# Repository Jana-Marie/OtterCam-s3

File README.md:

# OtterCam-s3

Open source 1080p60Hz USB & IP camera based on Sochip s3 and OS05A10/OS05A20 (general MIPI CSI IP camera interface).

In the current state the camera does boot and the sensor shows up under linux, however no video or image files have been captured yet, as the sensor driver is currently being written by us. All hardware files are tested in the current revision and are, except for some minor changes, final. Still no waranty as this is an open source project. CAD files have been designed with OpenSCAD and should be final too.

<table>
  <tbody>
    <tr>
      <td>
        
      </td>
      <td>
        
      </td>
    </tr>
    <tr>
      <td colspan="2">
        
      </td>
    </tr>
    <tr>
      <td>
        
      </td>
      <td>
        
      </td>
    </tr>
  </tbody>
</table>

### Todo
 - [ ] Test mipi driver
 - [ ] Build userspace code

### Issues
 - [x] MIPI Lanes Sensor are switched
 - [x] No I2C Pullups

### License

Copyright Jana Marie Hemsing 2023.

This source describes Open Hardware and is licensed under the CERN-OHL-S v2.

You may redistribute and modify this source and make products using it under
the terms of the CERN-OHL-S v2 (https://ohwr.org/cern_ohl_s_v2.txt).

This source is distributed WITHOUT ANY EXPRESS OR IMPLIED WARRANTY,
INCLUDING OF MERCHANTABILITY, SATISFACTORY QUALITY AND FITNESS FOR A
PARTICULAR PURPOSE. Please see the CERN-OHL-S v2 for applicable conditions.

Source location: https://github.com/Jana-Marie/OtterCam-s3

As per CERN-OHL-S v2 section 4, should You produce hardware based on this
source, You must where practicable maintain the Source Location visible
on the external case of the Gizmo or other products you make using this
source.

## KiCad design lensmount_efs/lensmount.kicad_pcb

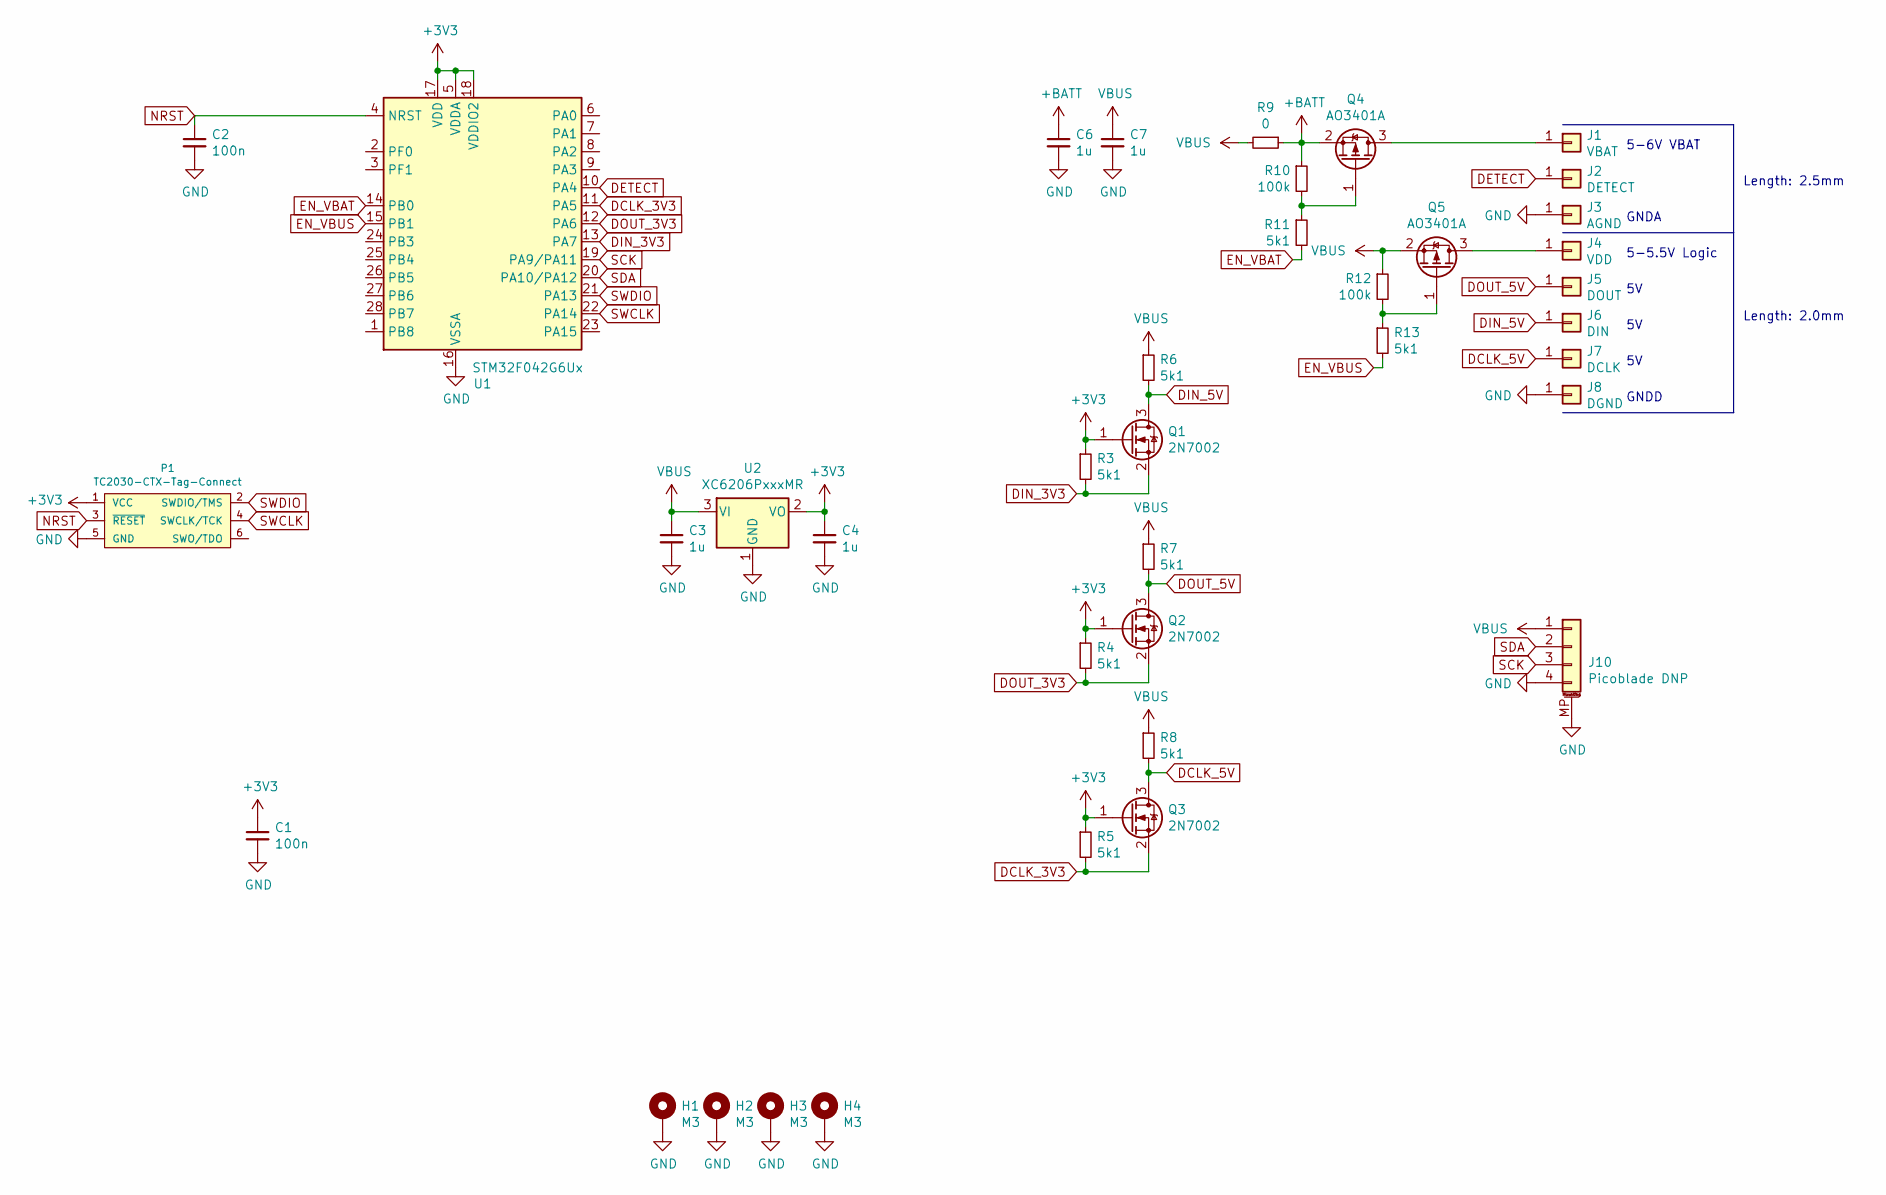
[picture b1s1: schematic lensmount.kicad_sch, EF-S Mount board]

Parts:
C1, C2: 100n; C_0402
C3, C4, C6, C7: 1u; C_0603
H1, H2, H3, H4: M3; MountingHole_3mm_Pad_Via
J1: VBAT; PH-MVF-5365; Mouser 581-709150001025006
J2: DETECT; PH-MVF-5365; Mouser 581-709150001025006
J3: AGND; PH-MVF-5365; Mouser 581-709150001025006
J4: VDD; PH-MVF-5365; Mouser 581-709150001020006
J5: DOUT; PH-MVF-5365; Mouser 581-709150001020006
J6: DIN; PH-MVF-5365; Mouser 581-709150001020006
J7: DCLK; PH-MVF-5365; Mouser 581-709150001020006
J8: DGND; PH-MVF-5365; Mouser 581-709150001020006
J10: Picoblade DNP; Molex_PicoBlade_53398-0471_1x04-1MP_P1.25mm_Vertical
P1: TC2030-CTX-Tag-Connect; TC2030
Q1, Q2, Q3: 2N7002; SOT-23
Q4, Q5: AO3401A; SOT-23
R3, R4, R5, R6, R7, R8, R11, R13: 5k1; R_0402
R9: 0; R_0402
R10, R12: 100k; R_0402
U1: STM32F042G6Ux; QFN-28_4x4mm_P0.5mm
U2: XC6206PxxxMR; SOT-23

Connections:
+3V3: C1.1, C4.1, P1.1 (VCC), Q1.1 (G), Q2.1 (G), Q3.1 (G), R3.1, R4.1, R5.1, U1.5 (VDDA), U1.17 (VDD), U1.18 (VDDIO2), U2.2 (VO)
+BATT: C6.1, Q4.2 (S), R9.1, R10.1
DCLK_3V3: Q3.2 (S), R5.2, U1.11 (PA5)
DCLK_5V: J7.1, Q3.3 (D), R8.2
DETECT: J2.1, U1.10 (PA4)
DIN_3V3: Q1.2 (S), R3.2, U1.13 (PA7)
DIN_5V: J6.1, Q1.3 (D), R6.2
DOUT_3V3: Q2.2 (S), R4.2, U1.12 (PA6)
DOUT_5V: J5.1, Q2.3 (D), R7.2
EN_VBAT: R11.2, U1.14 (PB0)
EN_VBUS: R13.2, U1.15 (PB1)
GND: C1.2, C2.2, C3.2, C4.2, C6.2, C7.2, H1.1, H2.1, H3.1, H4.1, J3.1, J8.1, J10.4, J10.MP (MountPin), P1.5 (GND), U1.16 (VSSA), U2.1 (GND)
NRST: C2.1, P1.3 (~RESET), U1.4 (NRST)
unnamed: J1.1, Q4.3 (D)
unnamed: J4.1, Q5.3 (D)
unnamed: Q4.1 (G), R10.2, R11.1
unnamed: Q5.1 (G), R12.2, R13.1
SCK: J10.3, U1.19 (PA9/PA11)
SDA: J10.2, U1.20 (PA10/PA12)
SWCLK: P1.4 (SWCLK/TCK), U1.22 (PA14)
SWDIO: P1.2 (SWDIO/TMS), U1.21 (PA13)
VBUS: C3.1, C7.1, J10.1, Q5.2 (S), R6.1, R7.1, R8.1, R9.2, R12.1, U2.3 (VI)

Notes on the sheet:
GNDD
5-6V VBAT
Length: 2.5mm
5-5.5V Logic
GNDA
Length: 2.0mm

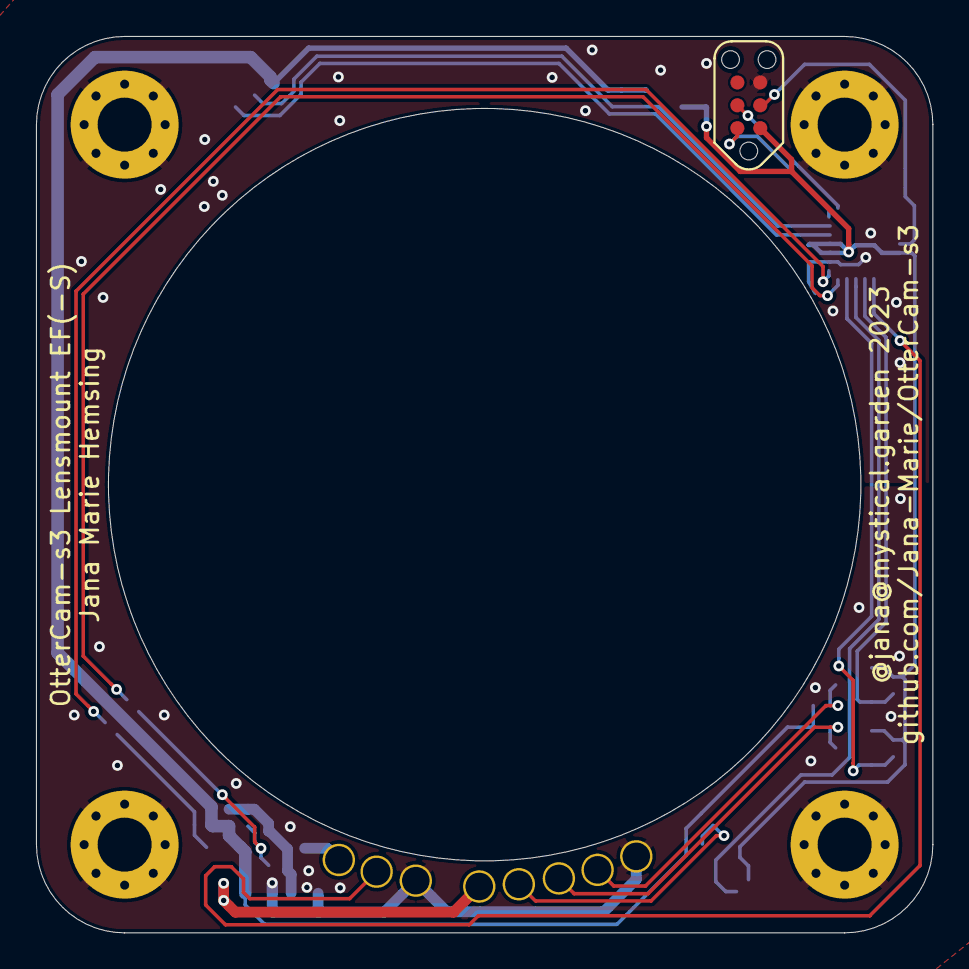
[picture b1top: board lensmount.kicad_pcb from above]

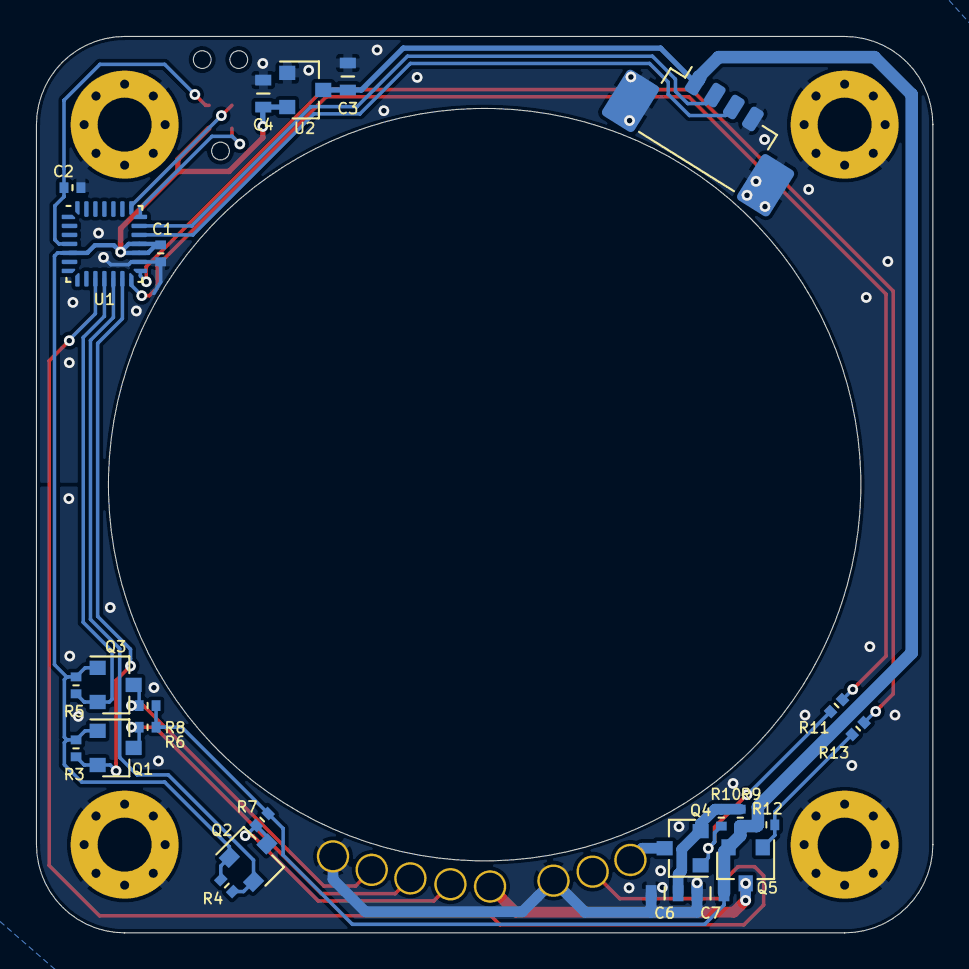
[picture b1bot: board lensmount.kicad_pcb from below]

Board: 2 copper layers, 49.8 x 49.8 mm, 38 parts (25 on the bottom side), 22 nets.

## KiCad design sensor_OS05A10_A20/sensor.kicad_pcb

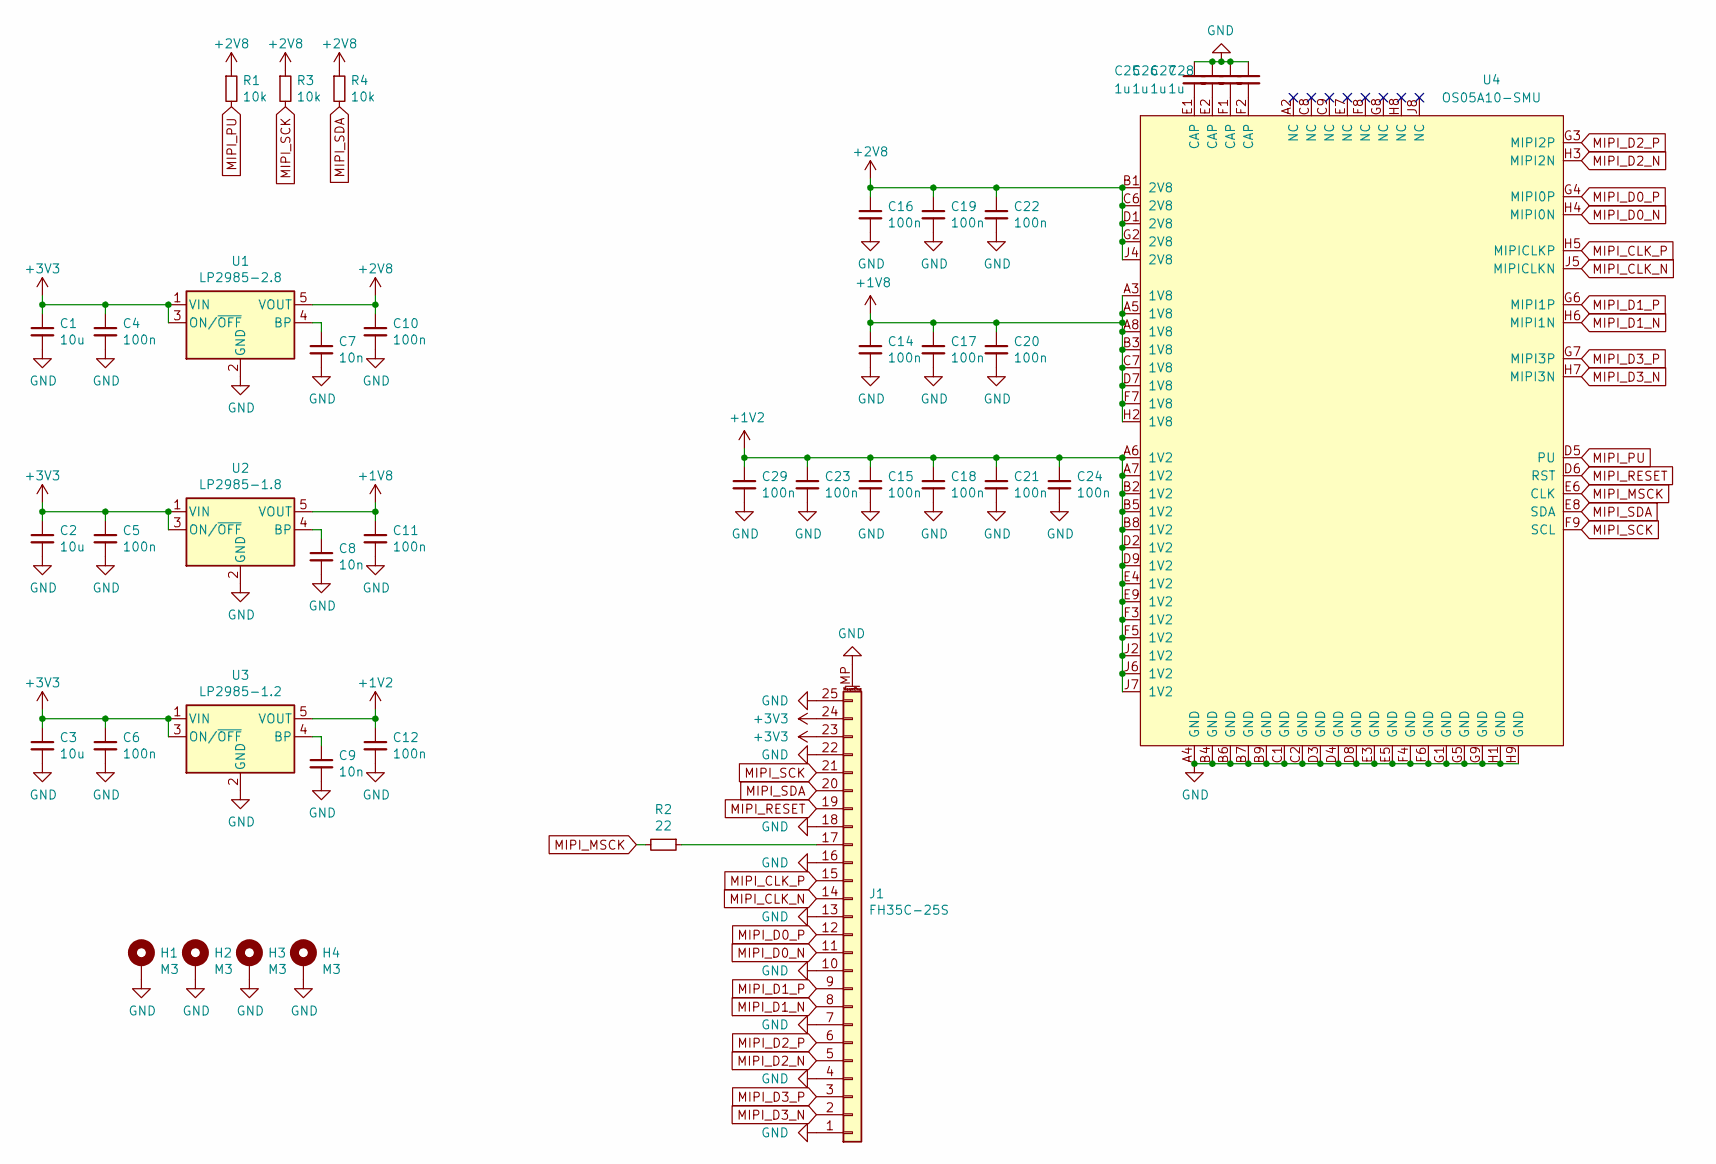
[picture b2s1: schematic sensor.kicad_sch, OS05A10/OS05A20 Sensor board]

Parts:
C1, C2, C3: 10u; C_0603
C4, C5, C6, C10, C11, C12, C14, C15, C16, C17, C18, C19, C20, C21, C22, C23, C24, C29: 100n; C_0402
C7, C8, C9: 10n; C_0402
C25, C26, C27, C28: 1u; C_0402
H1, H2, H3, H4: M3; MountingHole_3mm_Pad_Via
J1: FH35C-25S
R1, R3, R4: 10k; R_0402
R2: 22; R_0402
U1: LP2985-2.8; SOT-23-5
U2: LP2985-1.8; SOT-23-5
U3: LP2985-1.2; SOT-23-5
U4: OS05A10-SMU; OS05A10

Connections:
+1V2: C12.1, C15.1, C18.1, C21.1, C23.1, C24.1, C29.1, U3.5 (VOUT), U4.A6 (1V2), U4.A7 (1V2), U4.B2 (1V2), U4.B5 (1V2), U4.B8 (1V2), U4.D2 (1V2), U4.D9 (1V2), U4.E4 (1V2), U4.E9 (1V2), U4.F3 (1V2), U4.F5 (1V2), U4.J2 (1V2), U4.J6 (1V2), U4.J7 (1V2)
+1V8: C11.1, C14.1, C17.1, C20.1, U2.5 (VOUT), U4.A3 (1V8), U4.A5 (1V8), U4.A8 (1V8), U4.B3 (1V8), U4.C7 (1V8), U4.D7 (1V8), U4.F7 (1V8), U4.H2 (1V8)
+2V8: C10.1, C16.1, C19.1, C22.1, R1.1, R3.1, R4.1, U1.5 (VOUT), U4.B1 (2V8), U4.C6 (2V8), U4.D1 (2V8), U4.G2 (2V8), U4.J4 (2V8)
+3V3: C1.1, C2.1, C3.1, C4.1, C5.1, C6.1, J1.23, J1.24, U1.1 (VIN), U1.3 (ON/~OFF), U2.1 (VIN), U2.3 (ON/~OFF), U3.1 (VIN), U3.3 (ON/~OFF)
GND: C1.2, C2.2, C3.2, C4.2, C5.2, C6.2, C7.2, C8.2, C9.2, C10.2, C11.2, C12.2, C14.2, C15.2, C16.2, C17.2, C18.2, C19.2, C20.2, C21.2, C22.2, C23.2, C24.2, C25.1, C26.1, C27.1, C28.1, C29.2, H1.1, H2.1, H3.1, H4.1, J1.1, J1.4, J1.7, J1.10, J1.13, J1.16, J1.18, J1.22, J1.25, J1.MP (MountPin), U1.2 (GND), U2.2 (GND), U3.2 (GND), U4.A4 (GND), U4.B4 (GND), U4.B6 (GND), U4.B7 (GND), U4.B9 (GND), U4.C1 (GND), U4.C2 (GND), U4.D3 (GND), U4.D4 (GND), U4.D8 (GND), U4.E3 (GND), U4.E5 (GND), U4.F4 (GND), U4.F6 (GND), U4.G1 (GND), U4.G5 (GND), U4.G9 (GND), U4.H1 (GND), U4.H9 (GND)
MIPI_CLK_N: J1.14, U4.J5 (MIPICLKN)
MIPI_CLK_P: J1.15, U4.H5 (MIPICLKP)
MIPI_D0_N: J1.11, U4.H4 (MIPI0N)
MIPI_D0_P: J1.12, U4.G4 (MIPI0P)
MIPI_D1_N: J1.8, U4.H6 (MIPI1N)
MIPI_D1_P: J1.9, U4.G6 (MIPI1P)
MIPI_D2_N: J1.5, U4.H3 (MIPI2N)
MIPI_D2_P: J1.6, U4.G3 (MIPI2P)
MIPI_D3_N: J1.2, U4.H7 (MIPI3N)
MIPI_D3_P: J1.3, U4.G7 (MIPI3P)
MIPI_MSCK: R2.2, U4.E6 (CLK)
MIPI_PU: R1.2, U4.D5 (PU)
MIPI_RESET: J1.19, U4.D6 (RST)
MIPI_SCK: J1.21, R3.2, U4.F9 (SCL)
MIPI_SDA: J1.20, R4.2, U4.E8 (SDA)
unnamed: C7.1, U1.4 (BP)
unnamed: C8.1, U2.4 (BP)
unnamed: C9.1, U3.4 (BP)
unnamed: C25.2, U4.E1 (CAP)
unnamed: C26.2, U4.E2 (CAP)
unnamed: C27.2, U4.F1 (CAP)
unnamed: C28.2, U4.F2 (CAP)
unnamed: J1.17, R2.1

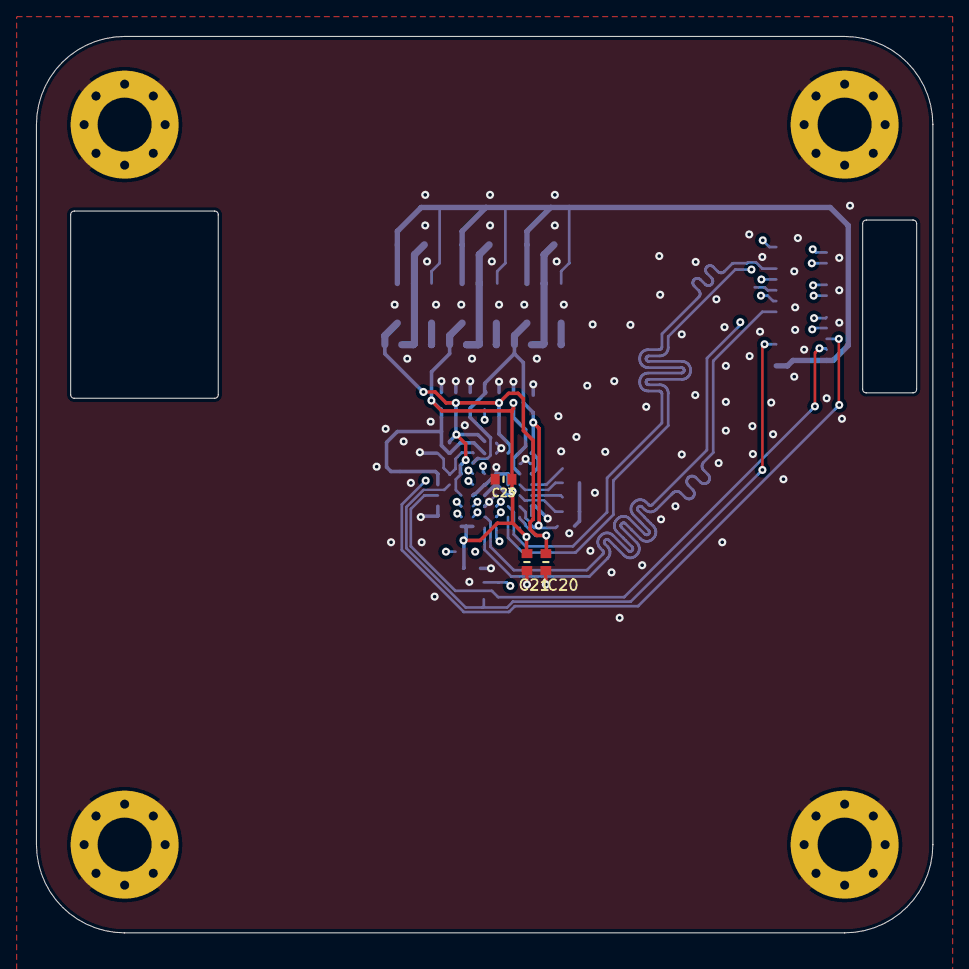
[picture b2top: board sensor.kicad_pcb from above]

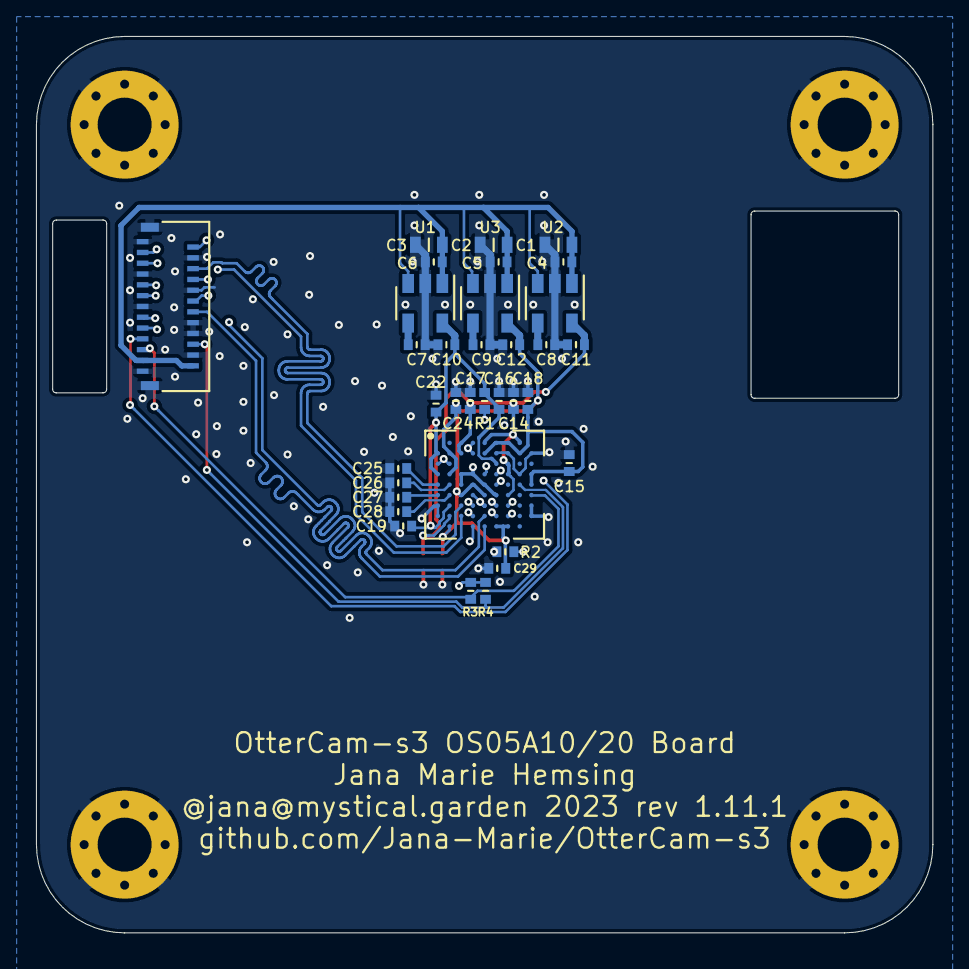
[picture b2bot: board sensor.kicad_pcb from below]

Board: 4 copper layers, 49.8 x 49.8 mm, 41 parts (38 on the bottom side), 28 nets.

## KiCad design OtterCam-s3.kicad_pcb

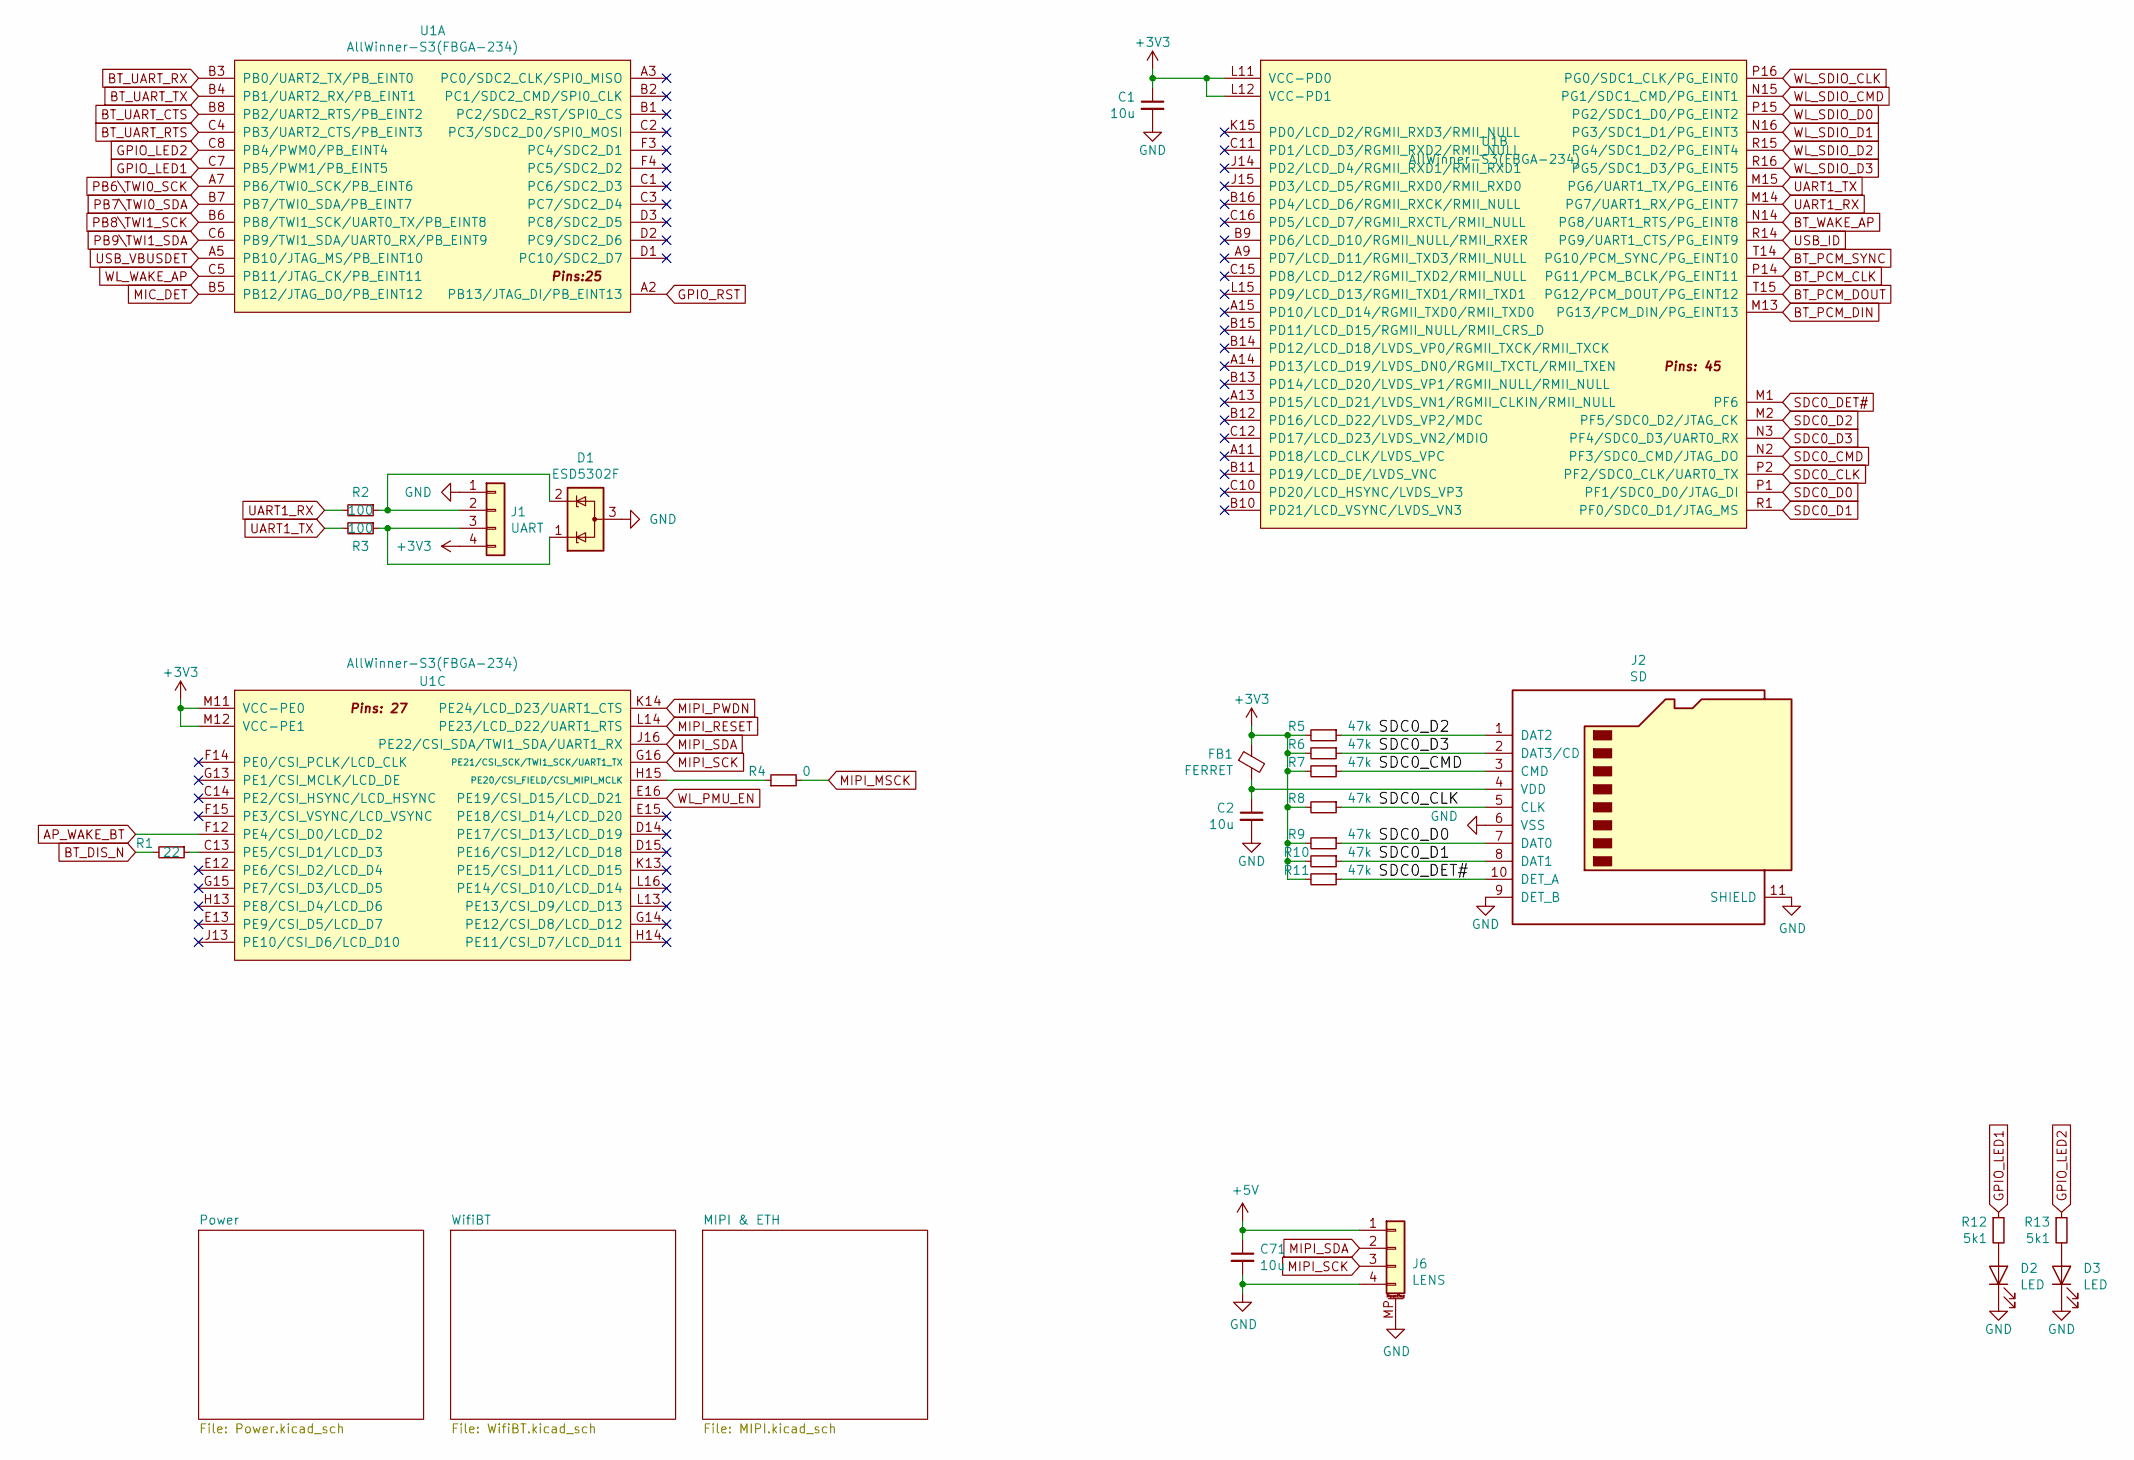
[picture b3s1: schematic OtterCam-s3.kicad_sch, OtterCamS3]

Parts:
C1, C2, C71: 10u; C_0603
D1: ESD5302F; SOT-23; LCSC C239643
D2, D3: LED; LED_0603_1608Metric
FB1: FERRET; R_0805
J1: UART; PinHeader_1x04_P2.00mm_Vertical_nosilk_center
J2: SD; microSD_HC_Hirose_DM3D-SF
J6: LENS; Molex_PicoBlade_53398-0471_1x04-1MP_P1.25mm_Vertical
R1: 22; R_0402
R2, R3: 100; R_0402
R4: 0; R_0402
R5, R6, R7, R8, R9, R10, R11: 47k; R_0402
R12, R13: 5k1; R_0402
U1: AllWinner-S3(FBGA-234); FBGA-234(Pitch-0.65mm_Pad-0.3mm_11x11x1.08mm)

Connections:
+3V3: C1.1, FB1.1, J1.4, R5.2, R6.2, R7.2, R8.2, R9.2, R10.2, R11.2, U1.L11 (VCC-PD0), U1.L12 (VCC-PD1), U1.M11 (VCC-PE0), U1.M12 (VCC-PE1); also elsewhere on the board
+5V: C71.1, J6.1; also elsewhere on the board
AP_WAKE_BT: U1.F12 (PE4/CSI_D0/LCD_D2); also elsewhere on the board
BT_DIS_N: R1.2; also elsewhere on the board
BT_PCM_CLK: U1.P14 (PG11/PCM_BCLK/PG_EINT11)
BT_PCM_DIN: U1.M13 (PG13/PCM_DIN/PG_EINT13)
BT_PCM_DOUT: U1.T15 (PG12/PCM_DOUT/PG_EINT12)
BT_PCM_SYNC: U1.T14 (PG10/PCM_SYNC/PG_EINT10)
BT_UART_CTS: U1.B8 (PB2/UART2_RTS/PB_EINT2); also elsewhere on the board
BT_UART_RTS: U1.C4 (PB3/UART2_CTS/PB_EINT3); also elsewhere on the board
BT_UART_RX: U1.B3 (PB0/UART2_TX/PB_EINT0); also elsewhere on the board
BT_UART_TX: U1.B4 (PB1/UART2_RX/PB_EINT1); also elsewhere on the board
BT_WAKE_AP: U1.N14 (PG8/UART1_RTS/PG_EINT8); also elsewhere on the board
GND: C1.2, C2.2, C71.2, D1.3 (A), D2.1 (K), D3.1 (K), J1.1, J2.6 (VSS), J2.9 (DET_B), J2.11 (SHIELD), J6.4, J6.MP (MountPin); also elsewhere on the board
GPIO_LED1: R12.1, U1.C7 (PB5/PWM1/PB_EINT5)
GPIO_LED2: R13.1, U1.C8 (PB4/PWM0/PB_EINT4)
GPIO_RST: U1.A2 (PB13/JTAG_DI/PB_EINT13); also elsewhere on the board
MIC_DET: U1.B5 (PB12/JTAG_DO/PB_EINT12)
MIPI_MSCK: R4.2; also elsewhere on the board
MIPI_PWDN: U1.K14 (PE24/LCD_D23/UART1_CTS)
MIPI_RESET: U1.L14 (PE23/LCD_D22/UART1_RTS); also elsewhere on the board
MIPI_SCK: J6.3, U1.G16 (PE21/CSI_SCK/TWI1_SCK/UART1_TX); also elsewhere on the board
MIPI_SDA: J6.2, U1.J16 (PE22/CSI_SDA/TWI1_SDA/UART1_RX); also elsewhere on the board
unnamed: C2.1, FB1.2, J2.4 (VDD)
unnamed: D1.1 (K), J1.3, R3.1
unnamed: D1.2 (K), J1.2, R2.1
unnamed: D2.2 (A), R12.2
unnamed: D3.2 (A), R13.2
unnamed: R1.1, U1.C13 (PE5/CSI_D1/LCD_D3)
unnamed: R4.1, U1.H15 (PE20/CSI_FIELD/CSI_MIPI_MCLK)
PB6\TWI0_SCK: U1.A7 (PB6/TWI0_SCK/PB_EINT6)
PB7\TWI0_SDA: U1.B7 (PB7/TWI0_SDA/PB_EINT7)
PB8\TWI1_SCK: U1.B6 (PB8/TWI1_SCK/UART0_TX/PB_EINT8)
PB9\TWI1_SDA: U1.C6 (PB9/TWI1_SDA/UART0_RX/PB_EINT9)
SDC0_CLK: J2.5 (CLK), R8.1, U1.P2 (PF2/SDC0_CLK/UART0_TX)
SDC0_CMD: J2.3 (CMD), R7.1, U1.N2 (PF3/SDC0_CMD/JTAG_DO)
SDC0_D0: J2.7 (DAT0), R9.1, U1.P1 (PF1/SDC0_D0/JTAG_DI)
SDC0_D1: J2.8 (DAT1), R10.1, U1.R1 (PF0/SDC0_D1/JTAG_MS)
SDC0_D2: J2.1 (DAT2), R5.1, U1.M2 (PF5/SDC0_D2/JTAG_CK)
SDC0_D3: J2.2 (DAT3/CD), R6.1, U1.N3 (PF4/SDC0_D3/UART0_RX)
SDC0_DET#: J2.10 (DET_A), R11.1, U1.M1 (PF6)
UART1_RX: R2.2, U1.M14 (PG7/UART1_RX/PG_EINT7)
UART1_TX: R3.2, U1.M15 (PG6/UART1_TX/PG_EINT6)
USB_ID: U1.R14 (PG9/UART1_CTS/PG_EINT9); also elsewhere on the board
USB_VBUSDET: U1.A5 (PB10/JTAG_MS/PB_EINT10)
WL_PMU_EN: U1.E16 (PE19/CSI_D15/LCD_D21); also elsewhere on the board
WL_SDIO_CLK: U1.P16 (PG0/SDC1_CLK/PG_EINT0); also elsewhere on the board
WL_SDIO_CMD: U1.N15 (PG1/SDC1_CMD/PG_EINT1); also elsewhere on the board
WL_SDIO_D0: U1.P15 (PG2/SDC1_D0/PG_EINT2); also elsewhere on the board
WL_SDIO_D1: U1.N16 (PG3/SDC1_D1/PG_EINT3); also elsewhere on the board
WL_SDIO_D2: U1.R15 (PG4/SDC1_D2/PG_EINT4); also elsewhere on the board
WL_SDIO_D3: U1.R16 (PG5/SDC1_D3/PG_EINT5); also elsewhere on the board
WL_WAKE_AP: U1.C5 (PB11/JTAG_CK/PB_EINT11); also elsewhere on the board

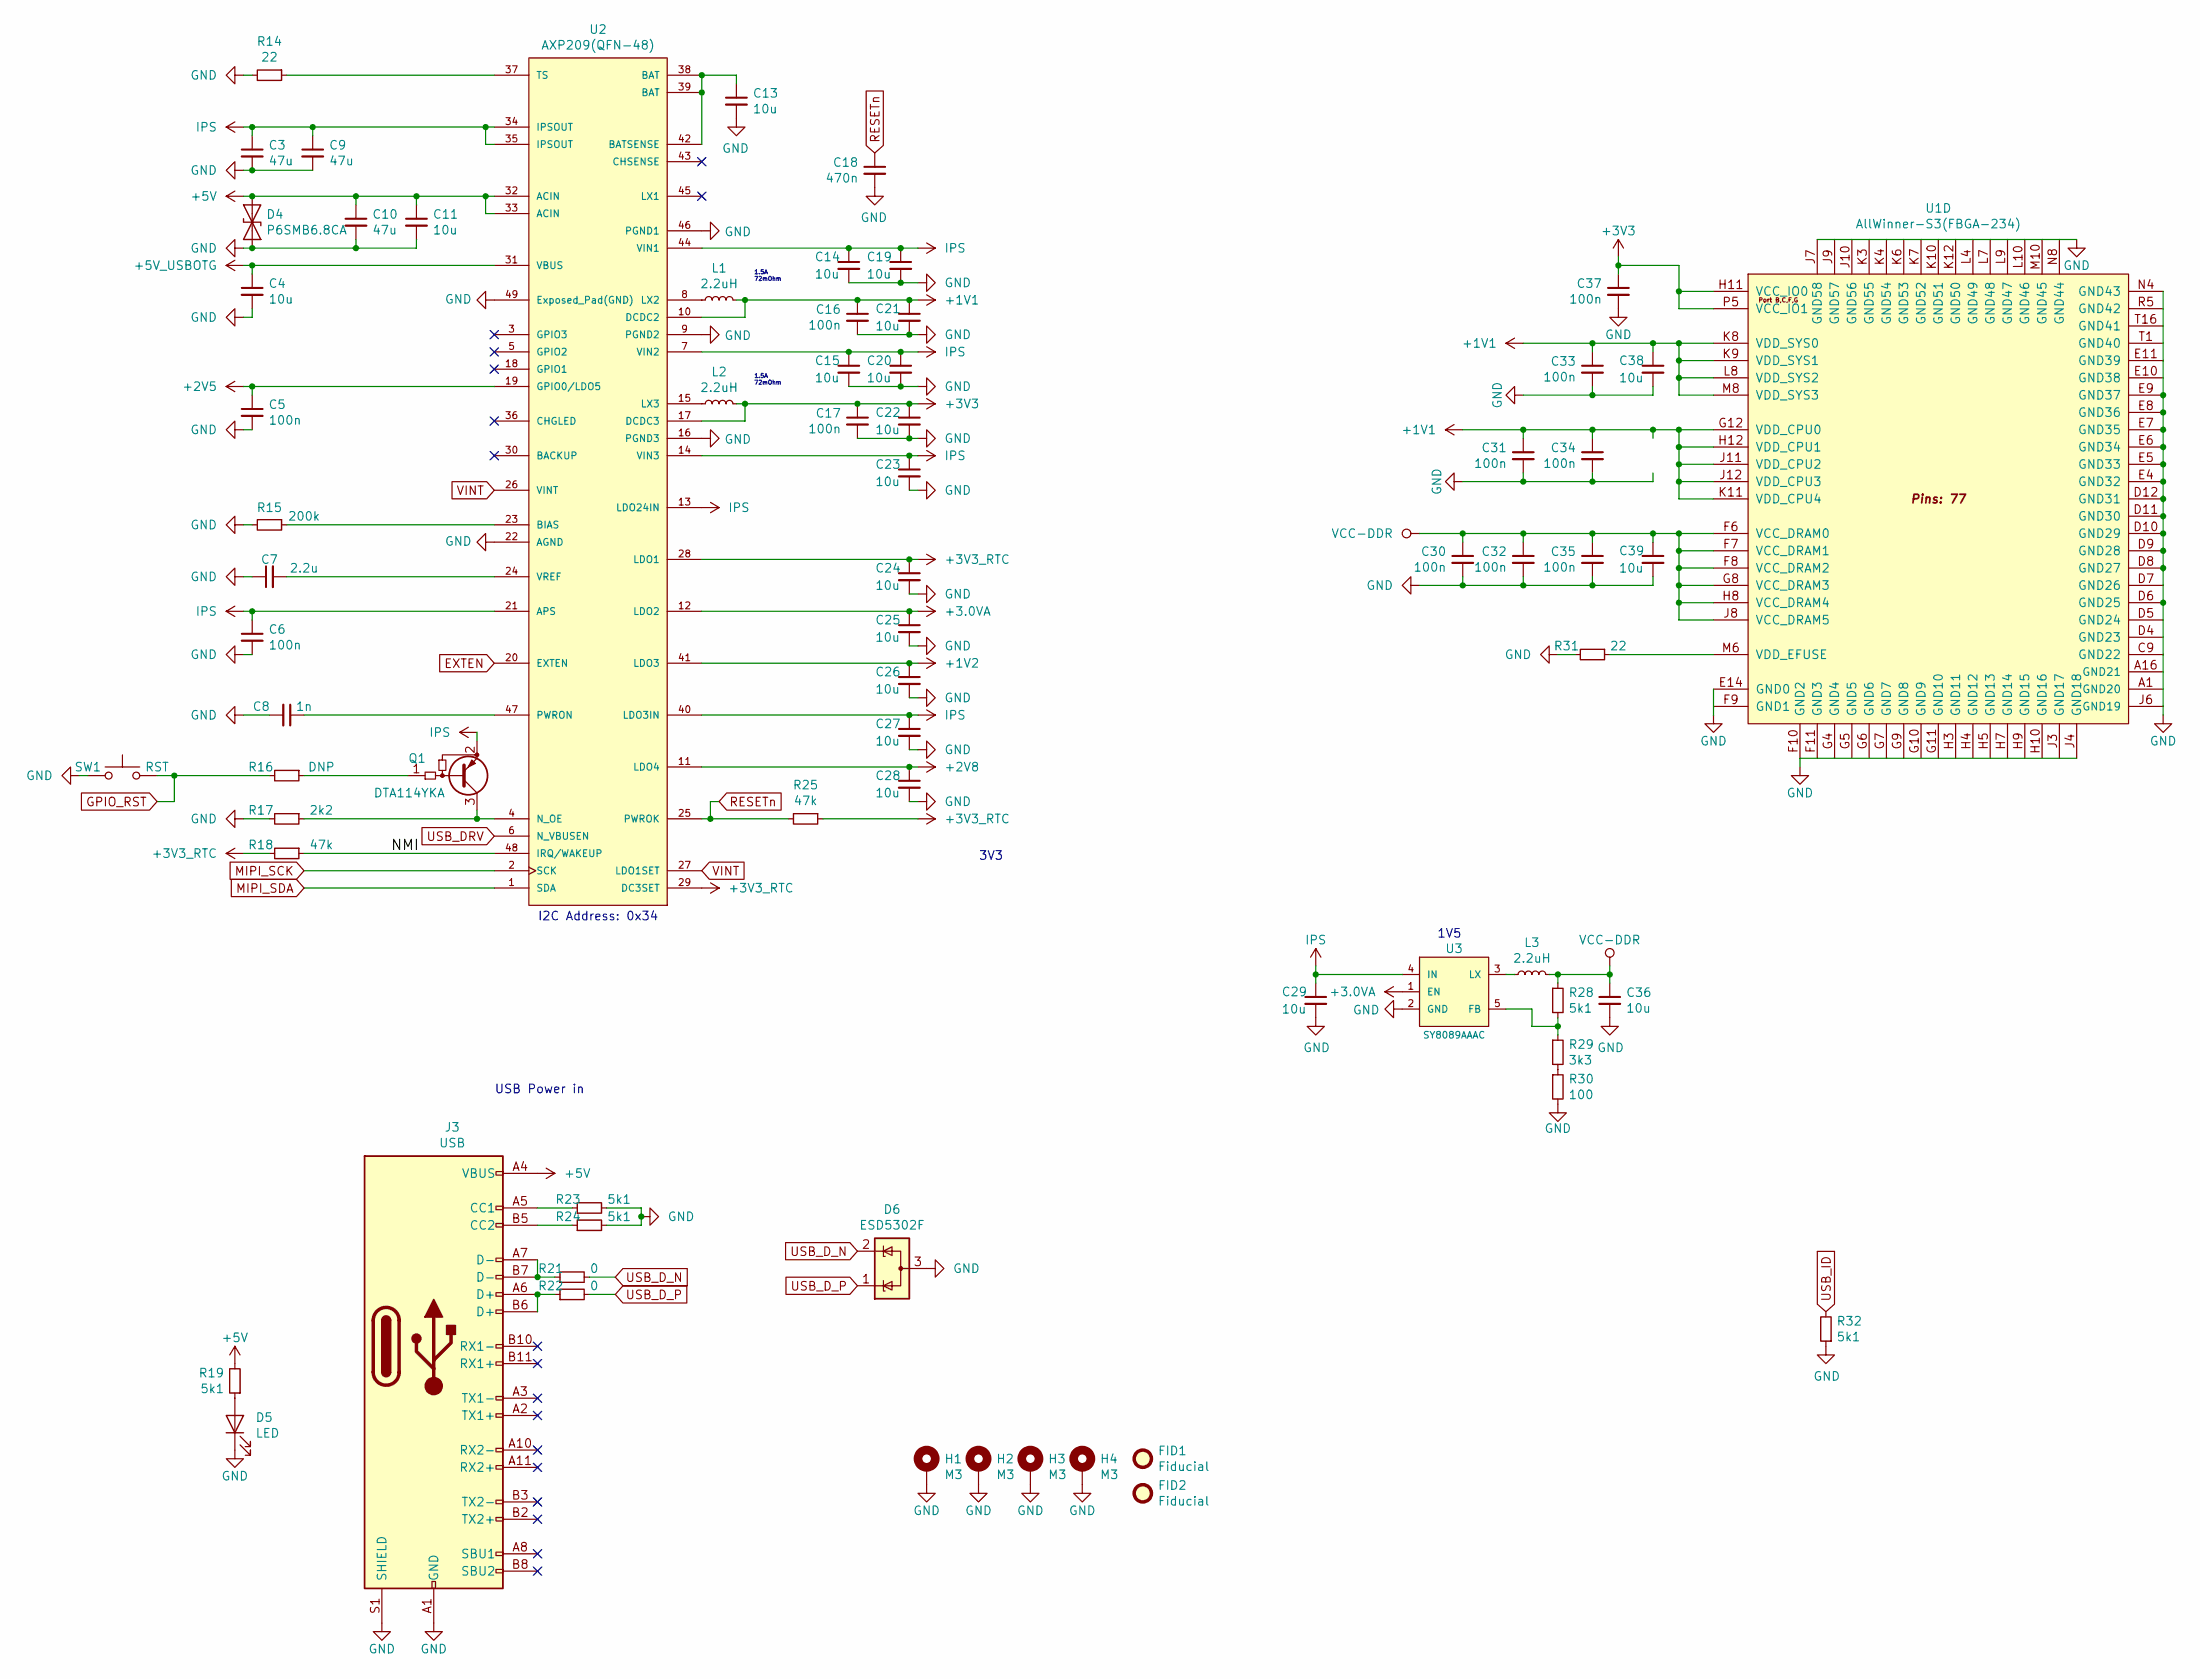
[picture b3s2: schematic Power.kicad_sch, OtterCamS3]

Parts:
C3, C9, C10: 47u; C_0805
C4, C11, C13, C14, C15, C19, C20, C21, C22, C23, C24, C25, C26, C27, C28, C29, C36, C38, C39: 10u; C_0603
C5, C6, C16, C17, C30, C31, C32, C33, C34, C35, C37: 100n; C_0402
C7: 2.2u; C_0603
C8: 1n; C_0402
C18: 470n; C_0402
D4: P6SMB6.8CA; D_SMB
D5: LED; LED_0603_1608Metric_Castellated
D6: ESD5302F; SOT-23; LCSC C239643
FID1, FID2: Fiducial; FID_1.52
H1, H2, H3, H4: M3; MountingHole_3mm_Pad_Via
J3: USB; 918-418K2022Y40004
L1, L2, L3: 2.2uH; L_Taiyo-Yuden_MD-3030; LCSC C167747
Q1: DTA114YKA; SOT-23
R14, R31: 22; R_0402
R15: 200k; R_0402
R16: DNP; R_0402
R17: 2k2; R_0402
R18, R25: 47k; R_0402
R19, R23, R24, R28, R32: 5k1; R_0402
R21, R22: 0; R_0402
R29: 3k3; R_0402
R30: 100; R_0402
SW1: RST; SW_SPST_PTS810
U1: AllWinner-S3(FBGA-234); FBGA-234(Pitch-0.65mm_Pad-0.3mm_11x11x1.08mm)
U2: AXP209(QFN-48); QFN-48-1EP_6x6mm_P0.4mm_EP4.05x4.05mm
U3: SY8089AAAC; SOT-23-5

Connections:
+1V1: C16.1, C21.1, C31.1, C33.1, C34.1, C38.1, L1.2, U1.G12 (VDD_CPU0), U1.H12 (VDD_CPU1), U1.J11 (VDD_CPU2), U1.J12 (VDD_CPU3), U1.K8 (VDD_SYS0), U1.K9 (VDD_SYS1), U1.K11 (VDD_CPU4), U1.L8 (VDD_SYS2), U1.M8 (VDD_SYS3), U2.10 (DCDC2); also elsewhere on the board
+1V2: C26.1, U2.41 (LDO3)
+2V5: C5.1, U2.19 (GPIO0/LDO5)
+2V8: C28.1, U2.11 (LDO4)
+3.0VA: C25.1, U2.12 (LDO2), U3.1 (EN); also elsewhere on the board
+3.3V_RTC: C24.1, R18.2, R25.1, U2.28 (LDO1), U2.29 (DC3SET); also elsewhere on the board
+3V3: C17.1, C22.1, C37.1, L2.2, U1.H11 (VCC_IO0), U1.P5 (VCC_IO1), U2.17 (DCDC3); also elsewhere on the board
+5V: C10.1, C11.1, D4.1 (A1), J3.A4 (VBUS), J3.A9 (VBUS), J3.B4 (VBUS), J3.B9 (VBUS), R19.2, U2.32 (ACIN), U2.33 (ACIN); also elsewhere on the board
+5V_USBOTG: C4.1, U2.31 (VBUS)
/Power/NMI: R18.1, U2.48 (IRQ/WAKEUP)
EXTEN: U2.20 (EXTEN)
GND: C3.2, C4.2, C5.2, C6.2, C7.1, C8.2, C9.2, C10.2, C11.2, C13.2, C14.2, C15.2, C16.2, C17.2, C18.2, C19.2, C20.2, C21.2, C22.2, C23.2, C24.2, C25.2, C26.2, C27.2, C28.2, C29.2, C30.2, C31.2, C32.2, C33.2, C34.2, C35.2, C36.2, C37.2, C38.2, C39.2, D4.2 (A2), D5.1 (K), D6.3 (A), H1.1, H2.1, H3.1, H4.1, J3.A1 (GND), J3.A12 (GND), J3.B1 (GND), J3.B12 (GND), J3.S1 (SHIELD), R14.2, R15.2, R17.2, R23.2, R24.2, R30.2, R31.2, R32.1, SW1.1, U1.A1 (GND20), U1.A16 (GND21), U1.C9 (GND22), U1.D4 (GND23), U1.D5 (GND24), U1.D6 (GND25), U1.D7 (GND26), U1.D8 (GND27), U1.D9 (GND28), U1.D10 (GND29), U1.D11 (GND30), U1.D12 (GND31), U1.E4 (GND32), U1.E5 (GND33), U1.E6 (GND34), U1.E7 (GND35), U1.E8 (GND36), U1.E9 (GND37), U1.E10 (GND38), U1.E11 (GND39), U1.E14 (GND0), U1.F9 (GND1), U1.F10 (GND2), U1.F11 (GND3), U1.G4 (GND4), U1.G5 (GND5), U1.G6 (GND6), U1.G7 (GND7), U1.G9 (GND8), U1.G10 (GND9), U1.G11 (GND10), U1.H3 (GND11), U1.H4 (GND12), U1.H5 (GND13), U1.H7 (GND14), U1.H9 (GND15), U1.H10 (GND16), U1.J3 (GND17), U1.J4 (GND18), U1.J6 (GND19), U1.J7 (GND58), U1.J9 (GND57), U1.J10 (GND56), U1.K3 (GND55), U1.K4 (GND54), U1.K6 (GND53), U1.K7 (GND52), U1.K10 (GND51), U1.K12 (GND50), U1.L4 (GND49), U1.L7 (GND48), U1.L9 (GND47), U1.L10 (GND46), U1.M10 (GND45), U1.N4 (GND43), U1.N8 (GND44), U1.R5 (GND42), U1.T1 (GND40), U1.T16 (GND41), U2.9 (PGND2), U2.16 (PGND3), U2.22 (AGND), U2.46 (PGND1), U2.49 (Exposed_Pad(GND)), U3.2 (GND); also elsewhere on the board
GPIO_RST: R16.2, SW1.2; also elsewhere on the board
IPS: C3.1, C6.1, C9.1, C14.1, C15.1, C19.1, C20.1, C23.1, C27.1, C29.1, Q1.2 (E), U2.7 (VIN2), U2.13 (LDO24IN), U2.14 (VIN3), U2.21 (APS), U2.34 (IPSOUT), U2.35 (IPSOUT), U2.40 (LDO3IN), U2.44 (VIN1), U3.4 (IN)
MIPI_SCK: U2.2 (SCK); also elsewhere on the board
MIPI_SDA: U2.1 (SDA); also elsewhere on the board
unnamed: C7.2, U2.24 (VREF)
unnamed: C8.1, U2.47 (PWRON)
unnamed: C13.1, U2.38 (BAT), U2.39 (BAT), U2.42 (BATSENSE)
unnamed: D5.2 (A), R19.1
unnamed: J3.A5 (CC1), R23.1
unnamed: J3.A6 (D+), J3.B6 (D+), R22.1
unnamed: J3.A7 (D-), J3.B7 (D-), R21.1
unnamed: J3.B5 (CC2), R24.1
unnamed: L1.1, U2.8 (LX2)
unnamed: L2.1, U2.15 (LX3)
unnamed: L3.1, U3.3 (LX)
unnamed: Q1.1 (B), R16.1
unnamed: Q1.3 (C), R17.1, U2.4 (N_OE)
unnamed: R14.1, U2.37 (TS)
unnamed: R15.1, U2.23 (BIAS)
unnamed: R28.2, R29.1, U3.5 (FB)
unnamed: R29.2, R30.1
unnamed: R31.1, U1.M6 (VDD_EFUSE)
RESETn: C18.1, R25.2, U2.25 (PWROK); also elsewhere on the board
USB_DRV: U2.6 (N_VBUSEN)
USB_D_N: D6.2 (K), R21.2; also elsewhere on the board
USB_D_P: D6.1 (K), R22.2; also elsewhere on the board
USB_ID: R32.2; also elsewhere on the board
VCC-DDR: C30.1, C32.1, C35.1, C36.1, C39.1, L3.2, R28.1, U1.F6 (VCC_DRAM0), U1.F7 (VCC_DRAM1), U1.F8 (VCC_DRAM2), U1.G8 (VCC_DRAM3), U1.H8 (VCC_DRAM4), U1.J8 (VCC_DRAM5); also elsewhere on the board
VINT: U2.26 (VINT), U2.27 (LDO1SET)

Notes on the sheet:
1.5A 72mOhm
1V5
3V3
USB Power in
I2C Address: 0x34
